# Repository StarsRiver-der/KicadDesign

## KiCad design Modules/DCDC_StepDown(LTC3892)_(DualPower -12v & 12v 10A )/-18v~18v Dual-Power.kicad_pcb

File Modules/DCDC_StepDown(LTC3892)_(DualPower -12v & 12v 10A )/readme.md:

# 16V-55V 输入的 DCDC 双极性双轨电源
* 工作温度：0-85℃
* 16V-55V宽输
* -12V最大输出5A，12V最大输出10A (通过采样电阻配置)

# 原理
见说明手册

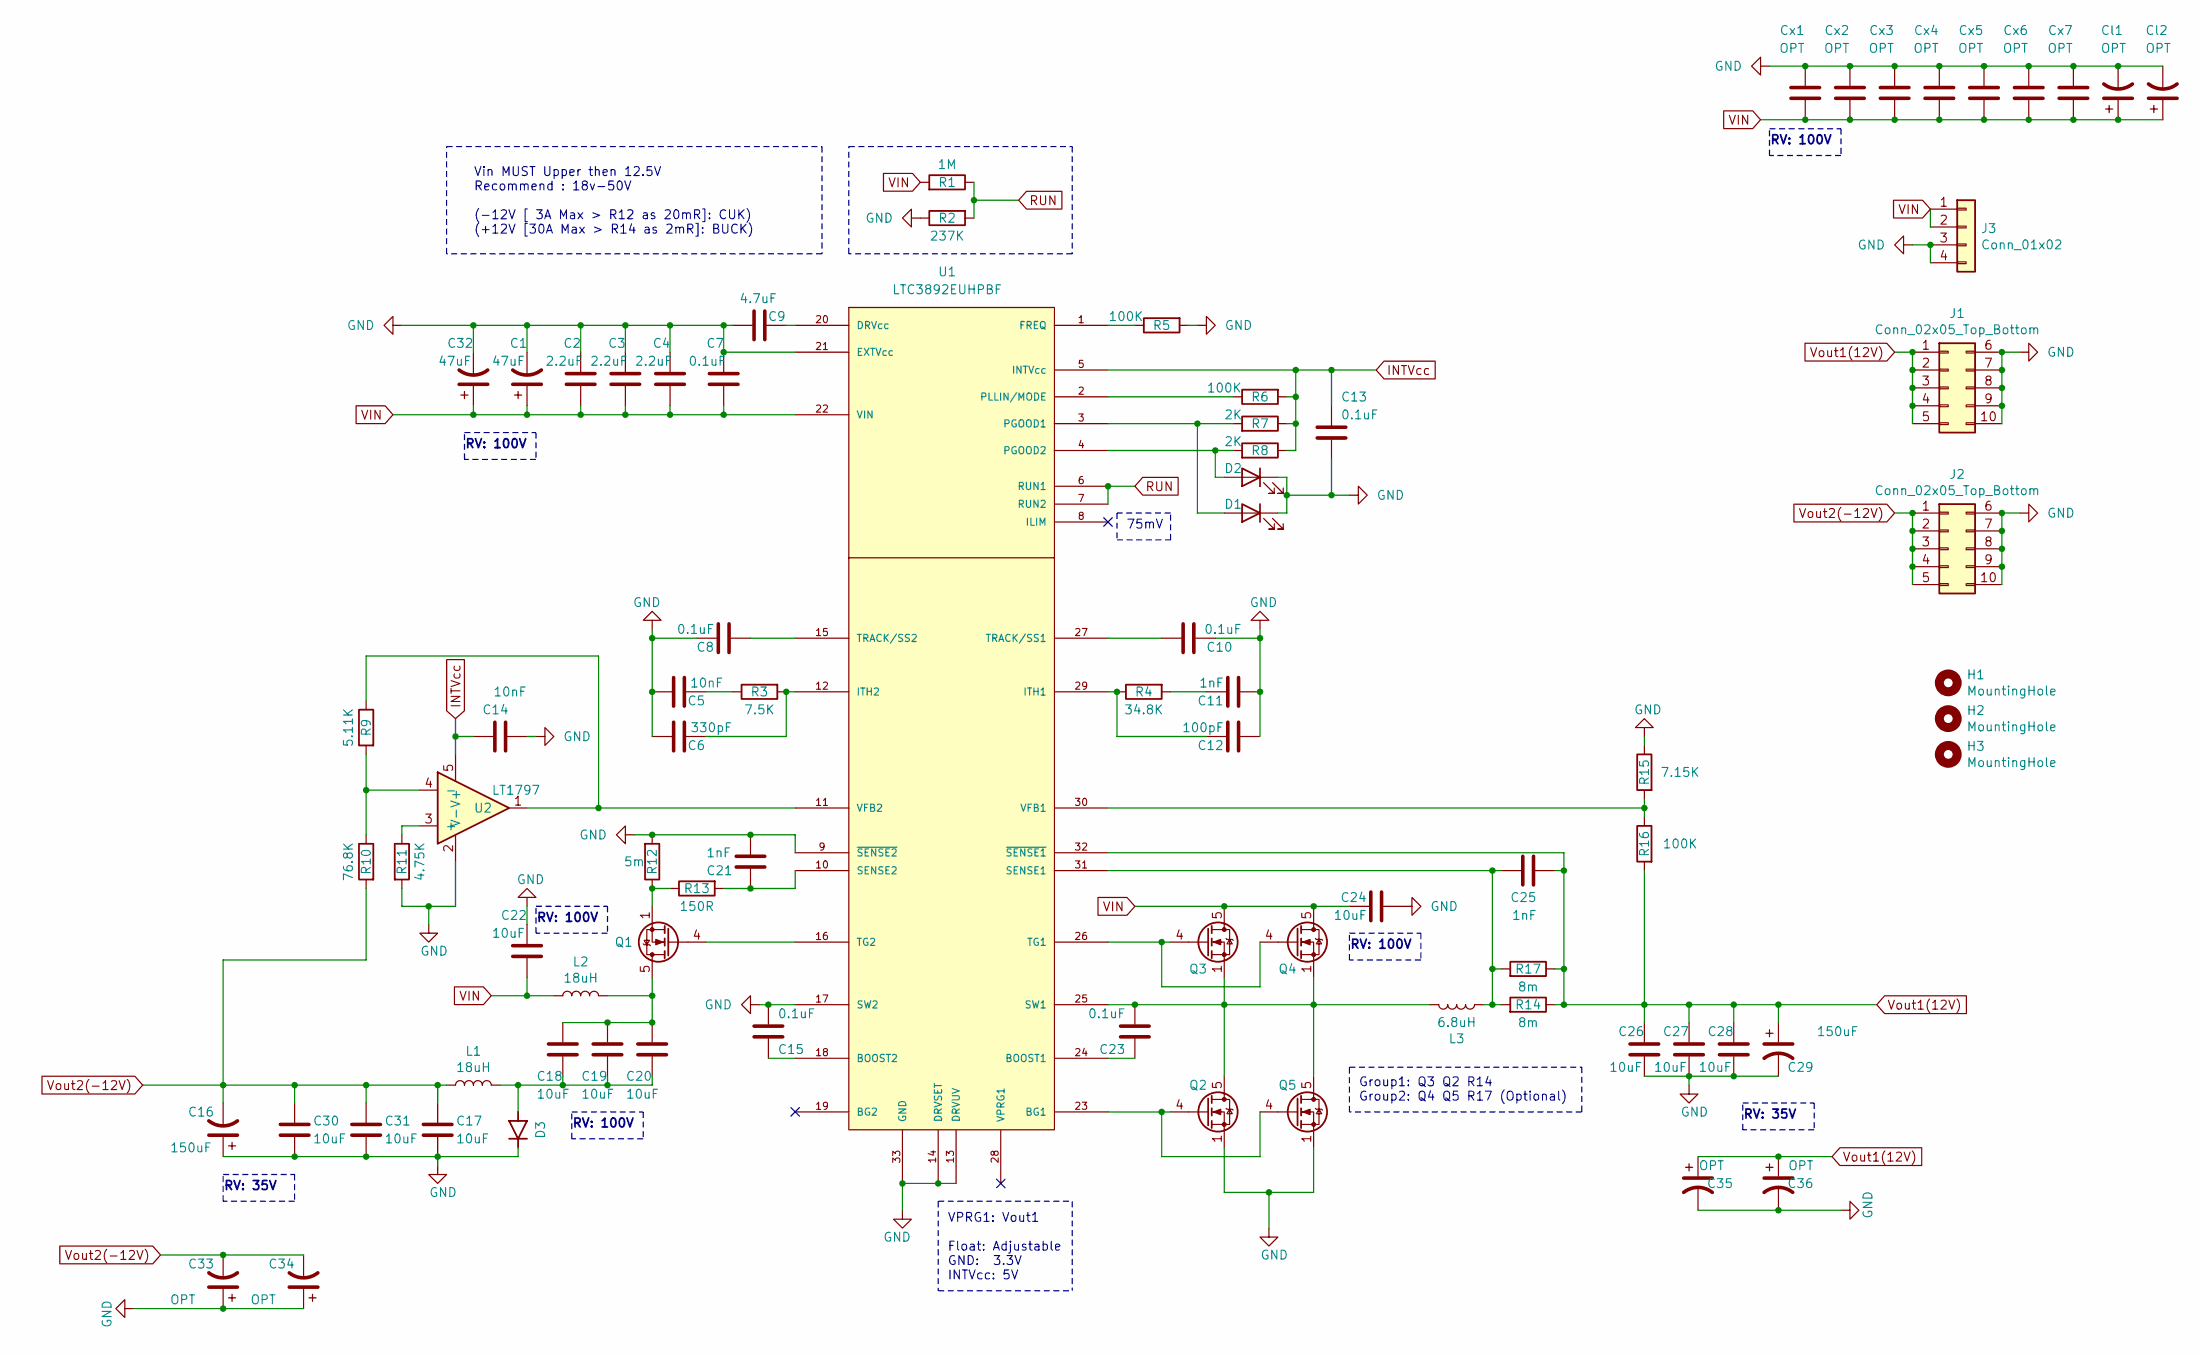
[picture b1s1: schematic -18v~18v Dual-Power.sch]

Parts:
C1, C32: 47uF; CP_Elec_10x10
C2, C3, C4: 2.2uF; C_1206_3216Metric
C5, C14: 10nF; C_0402_1005Metric
C6: 330pF; C_0402_1005Metric
C7, C23: 0.1uF; C_0603_1608Metric
C8, C10, C13, C15: 0.1uF; C_0402_1005Metric
C9: 4.7uF; C_0402_1005Metric
C11, C21, C25: 1nF; C_0402_1005Metric
C12: 100pF; C_0402_1005Metric
C16, C29: 150uF; CP_Elec_8x10
C17, C18, C19, C20, C22, C24, C26, C27, C28, C30, C31: 10uF; C_1206_3216Metric
C33, C34, C35, C36: OPT; CP_Elec_8x10
Cl1, Cl2: OPT; CP_Elec_10x10
Cx1, Cx2, Cx3, Cx4, Cx5, Cx6, Cx7: OPT; C_1206_3216Metric
D1, D2: LED; LED_0402_1005Metric
D3: SBR8U60P5-13; DIO_PDS360-13; MPN SBR8U60P5-13
H1, H2, H3: MountingHole; MountingHole_2.2mm_M2
J1, J2: Conn_02x05_Top_Bottom; Molex_Micro-Fit_3.0_43045-1012_2x05_P3.00mm_Vertical
J3: Conn_01x02; Molex_Mini-Fit_Jr_5566-04A_2x02_P4.20mm_Vertical
L1, L2: 18uH; L_Wuerth_HCM-1350
L3: 6.8uH; L_Wuerth_HCM-1350
Q1, Q2, Q3, Q4, Q5: BSC028N06LS3; TDSON-8-1
R1: 1M; R_0402_1005Metric
R2: 237K; R_0402_1005Metric
R3: 7.5K; R_0402_1005Metric
R4: 34.8K; R_0402_1005Metric
R5, R6, R16: 100K; R_0402_1005Metric
R7, R8: 2K; R_0402_1005Metric
R9: 5.11K; R_0402_1005Metric
R10: 76.8K; R_0402_1005Metric
R11: 4.75K; R_0402_1005Metric
R12: 5m; R_2512_6332Metric
R13: 150R; R_0402_1005Metric
R14, R17: 8m; R_2512_6332Metric
R15: 7.15K; R_0402_1005Metric
U1: LTC3892EUHPBF; QFN-32_UH; MANUFACTURER_PART_NUMBER ltc3892euh#pbf
U2: LT1797; SOT-23-5

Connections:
GND: C1.2, C2.2, C3.2, C4.2, C5.1, C6.1, C7.2, C8.1, C9.1, C10.2, C11.2, C12.2, C13.2, C14.2, C15.1, C16.1, C17.1, C21.1, C22.2, C24.2, C26.1, C27.1, C28.1, C29.2, C30.1, C31.1, C32.2, C33.1, C34.1, C35.2, C36.2, Cl1.2, Cl2.2, Cx1.1, Cx2.1, Cx3.1, Cx4.1, Cx5.1, Cx6.1, Cx7.1, D1.1 (K), D2.1 (K), D3.3, J1.6, J1.7, J1.8, J1.9, J1.10, J2.6, J2.7, J2.8, J2.9, J2.10, J3.3, J3.4, Q2.1 (S), Q2.2 (S), Q2.3 (S), Q5.1 (S), Q5.2 (S), Q5.3 (S), R2.1, R5.2, R11.2, R12.2, R15.1, U1.9 (~SENSE2), U1.13 (DRVUV), U1.14 (DRVSET), U1.17 (SW2), U1.21 (EXTVcc), U1.33 (GND), U2.2 (V-)
INTVcc: C13.1, C14.1, R6.2, R7.1, R8.1, U1.5 (INTVcc), U2.5 (V+)
unnamed: C5.2, R3.1
unnamed: C6.2, R3.2, U1.12 (ITH2)
unnamed: C8.2, U1.15 (TRACK/SS2)
unnamed: C9.2, U1.20 (DRVcc)
unnamed: C10.1, U1.27 (TRACK/SS1)
unnamed: C11.1, R4.2
unnamed: C12.1, R4.1, U1.29 (ITH1)
unnamed: C15.2, U1.18 (BOOST2)
unnamed: C18.1, C19.1, C20.1, D3.1, D3.2, L1.2
unnamed: C18.2, C19.2, C20.2, L2.2, Q1.5 (D)
unnamed: C21.2, R13.2, U1.10 (SENSE2)
unnamed: C23.1, L3.1, Q2.5 (D), Q3.1 (S), Q3.2 (S), Q3.3 (S), Q4.1 (S), Q4.2 (S), Q4.3 (S), Q5.5 (D), U1.25 (SW1)
unnamed: C23.2, U1.24 (BOOST1)
unnamed: C25.1, L3.2, R14.2, R17.2, U1.31 (SENSE1)
unnamed: D1.2 (A), R7.2, U1.3 (PGOOD1)
unnamed: D2.2 (A), R8.2, U1.4 (PGOOD2)
unnamed: Q1.1 (S), Q1.2 (S), Q1.3 (S), R12.1, R13.1
unnamed: Q1.4 (G), U1.16 (TG2)
unnamed: Q2.4 (G), Q5.4 (G), U1.23 (BG1)
unnamed: Q3.4 (G), Q4.4 (G), U1.26 (TG1)
unnamed: R5.1, U1.1 (FREQ)
unnamed: R6.1, U1.2 (PLLIN/MODE)
unnamed: R9.1, U1.11 (VFB2), U2.1
unnamed: R9.2, R10.1, U2.4 (-)
unnamed: R11.1, U2.3 (+)
unnamed: R15.2, R16.1, U1.30 (VFB1)
RUN: R1.1, R2.2, U1.6 (RUN1), U1.7 (RUN2)
VIN: C1.1, C2.1, C3.1, C4.1, C7.1, C22.1, C24.1, C32.1, Cl1.1, Cl2.1, Cx1.2, Cx2.2, Cx3.2, Cx4.2, Cx5.2, Cx6.2, Cx7.2, J3.1, J3.2, L2.1, Q3.5 (D), Q4.5 (D), R1.2, U1.22 (VIN)
Vout1(12V): C25.2, C26.2, C27.2, C28.2, C29.1, C35.1, C36.1, J1.1, J1.2, J1.3, J1.4, J1.5, R14.1, R16.2, R17.1, U1.32 (~SENSE1)
Vout2(-12V): C16.2, C17.2, C30.2, C31.2, C33.2, C34.2, J2.1, J2.2, J2.3, J2.4, J2.5, L1.1, R10.2

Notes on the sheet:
VPRG1: Vout1 Float: Adjustable GND: 3.3V INTVcc: 5V
75mV
Vin MUST Upper then 12.5V Recommend : 18v-50V (-12V [ 3A Max > R12 as 20mR]: CUK) (+12V [30A Max > R14 as 2mR]: BUCK)
Group1: Q3 Q2 R14 Group2: Q4 Q5 R17 (Optional)
RV: 100V
RV: 35V

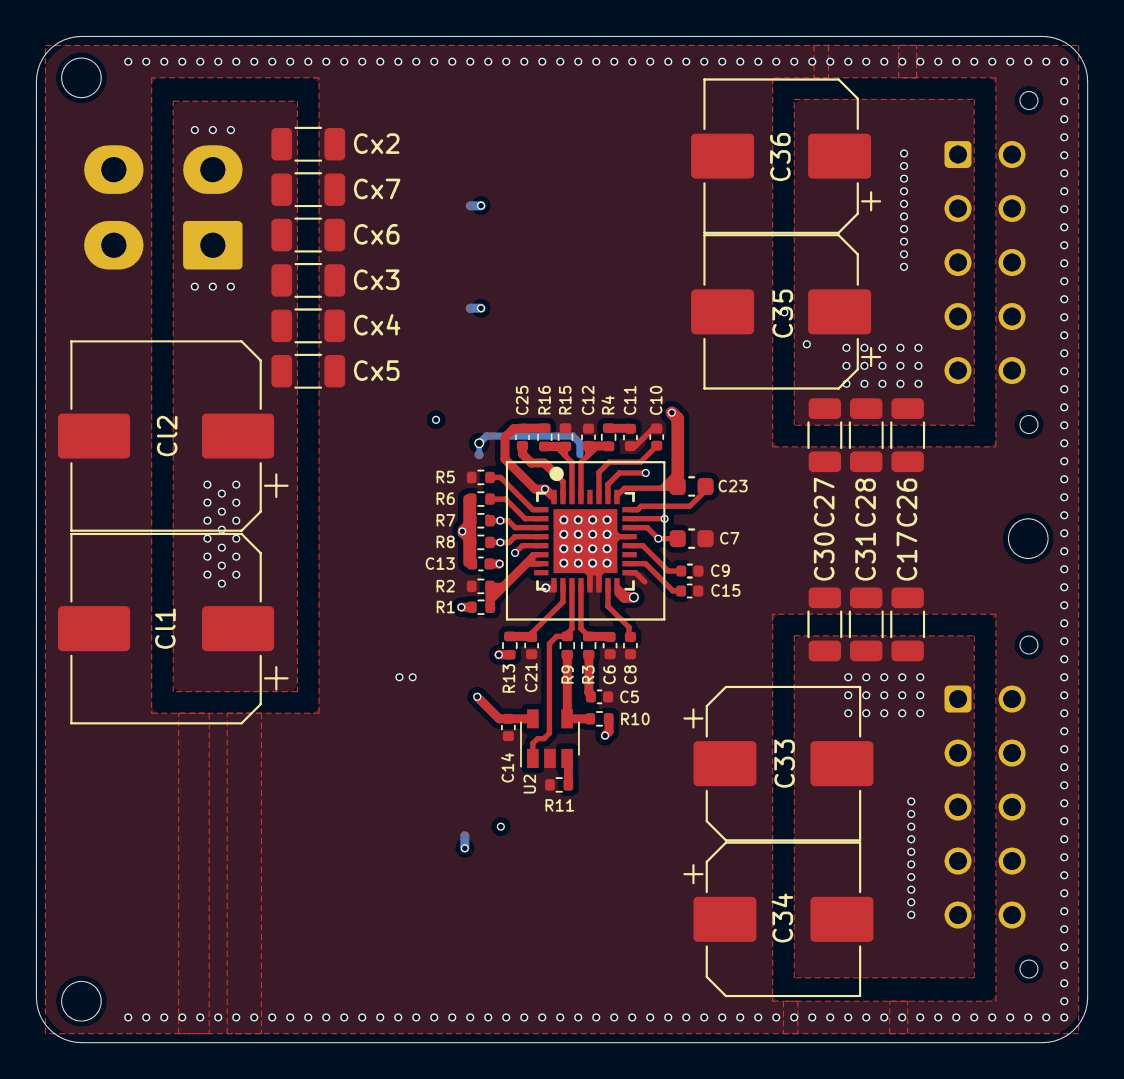
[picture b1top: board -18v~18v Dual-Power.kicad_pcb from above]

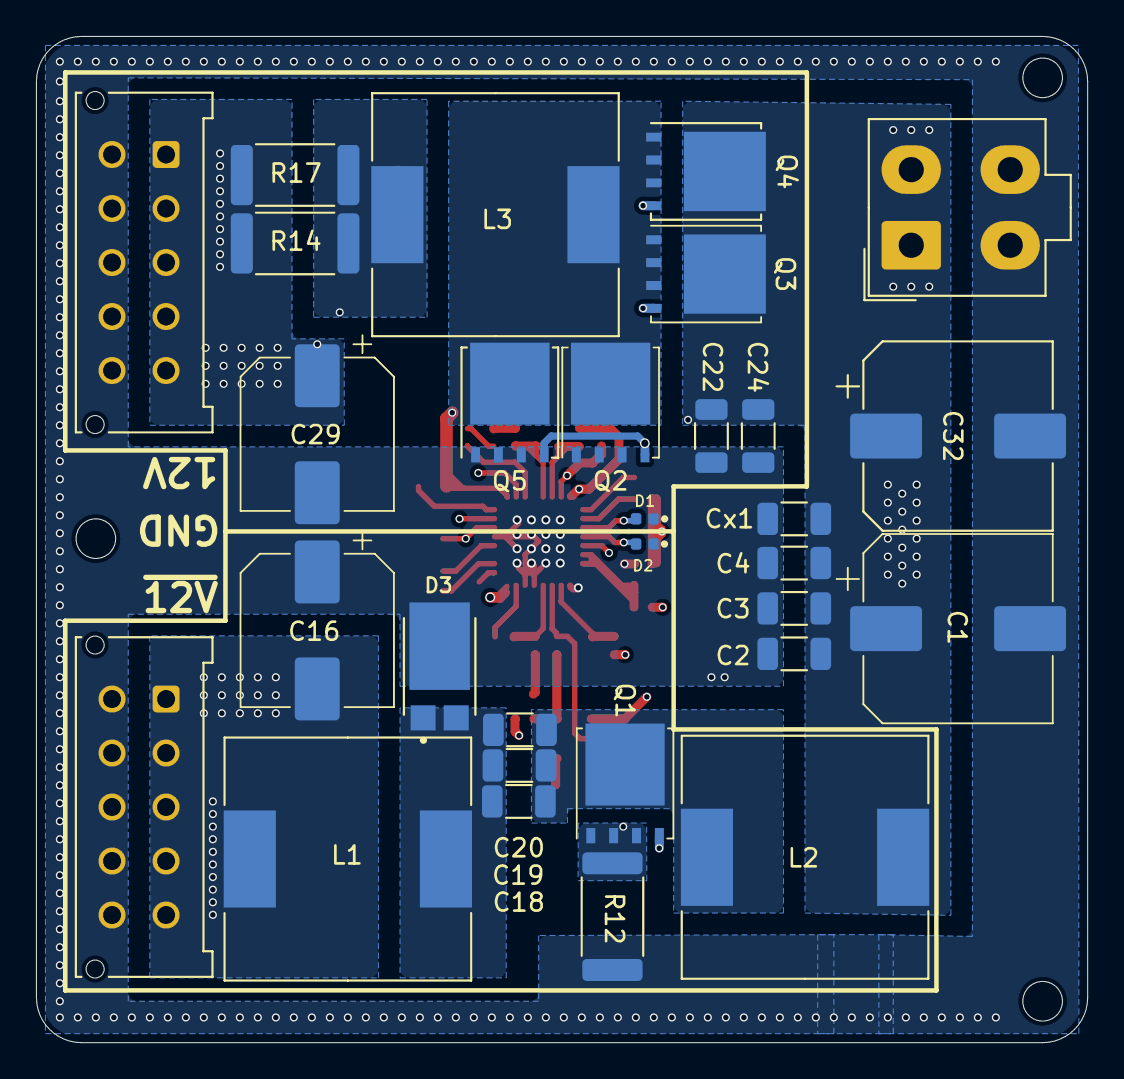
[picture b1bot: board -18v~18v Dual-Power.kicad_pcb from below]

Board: 4 copper layers, 58.4 x 55.9 mm, 81 parts (30 on the bottom side), 32 nets.

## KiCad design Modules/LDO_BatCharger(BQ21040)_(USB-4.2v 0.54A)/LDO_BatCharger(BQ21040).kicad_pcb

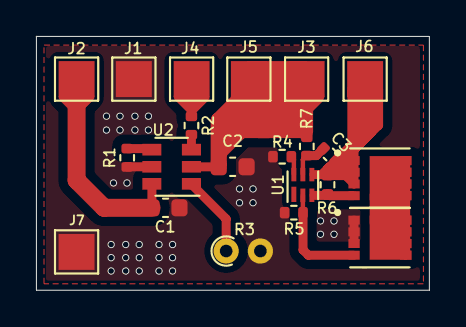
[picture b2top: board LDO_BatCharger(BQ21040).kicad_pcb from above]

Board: 2 copper layers, 21.8 x 14.1 mm, 21 parts (0 on the bottom side), 14 nets.

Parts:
C1, C2: 1uF; C_0603_1608Metric
C3: 0.1uF; C_0402_1005Metric
J1, J2, J3, J4, J5, J6, J7: Conn_01x01; TestPoint_Pad_2.0x2.0mm
R1, R2: 1K; R_0402_1005Metric
R3: 103AT-2; R_Axial_DIN0204_L3.6mm_D1.6mm_P1.90mm_Vertical
R4: 2.2k; R_0402_1005Metric
R5: 5.1M; R_0402_1005Metric
R6: 5.1m; R_0402_1005Metric
R7: 330R; R_0402_1005Metric
U1: BQ2970; WSON-6_1.5x1.5mm_P0.5mm
U2: BQ21040; SOT-23-6
U3, U4: CSD16406Q3

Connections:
Adapter+: C1.1, J2.1, U2.6
BAT+: C2.1, J3.1, J5.1, R7.1, U2.2
BAT-: C3.2, J6.1, R6.2, U1.4, U4.1
ChargeLight-: J4.1, R2.2
GND: C1.2, C2.2, J1.1, J7.1, R1.2, R3.2, R4.2, R5.2, U2.5, U3.1, U3.2, U3.3
unnamed: C3.1, R7.2, U1.5
unnamed: R1.1, U2.4
unnamed: R2.1, U2.3
unnamed: R3.1, U2.1
unnamed: R4.1, U1.6
unnamed: R5.1, U1.2, U3.4
unnamed: R6.1, U1.3, U4.4
unnamed: U3.5, U3.6, U3.7, U3.8, U4.5, U4.6, U4.7, U4.8
unnamed: U4.2, U4.3

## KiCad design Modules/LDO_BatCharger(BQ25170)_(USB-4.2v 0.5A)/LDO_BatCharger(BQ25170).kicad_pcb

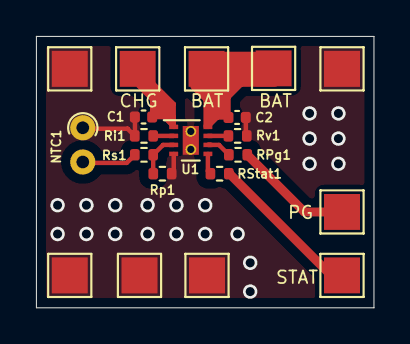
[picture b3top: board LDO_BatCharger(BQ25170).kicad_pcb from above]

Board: 2 copper layers, 18.8 x 15.1 mm, 20 parts (0 on the bottom side), 11 nets.

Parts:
C1, C2: 1uF; C_0402_1005Metric
J1, J2, J3, J4, J5, J5#2, J6, J7, J8, J9: Conn_01x01; TestPoint_Pad_2.0x2.0mm
NTC1: 103AT-2; R_Axial_DIN0204_L3.6mm_D1.6mm_P1.90mm_Vertical
RPg1: 10K; R_0402_1005Metric
RStat1: 10K; R_0402_1005Metric
Ri1: 600R; R_0402_1005Metric
Rp1: 400k; R_0402_1005Metric
Rs1: 1.9k; R_0402_1005Metric
Rv1: 27K; R_0402_1005Metric
U1: BQ25170; WSON-8-1EP_2x2mm_P0.5mm_EP0.9x1.6mm_ThermalVias

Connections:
BAT: C2.2, J1.1, J9.1, U1.8
GND: C1.2, C2.1, J4.1, J5.1, J5#2.1, J6.1, J7.1, NTC1.1, Ri1.2, Rp1.1, Rv1.2, U1.4, U1.9
IN: C1.1, J8.1, U1.1
unnamed: NTC1.2, Rs1.1
unnamed: RPg1.1, U1.6
unnamed: RStat1.1, U1.5
unnamed: Ri1.1, U1.2
unnamed: Rp1.2, Rs1.2, U1.3
unnamed: Rv1.1, U1.7
PG: J3.1, RPg1.2
STAT: J2.1, RStat1.2
